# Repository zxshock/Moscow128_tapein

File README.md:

# Moscow128_tapein
4069 / 561LN2 based tape-in circuit for Moscow 128 boards to replace/substitute the convoluted original circuit.  
Note: This is intended for the 1989/replica boards not modernized variants. About the size of a DIP-20 socket.  

Measurements unchecked as of now.  
Preview has GND/VCC swapped - fixed in .brd

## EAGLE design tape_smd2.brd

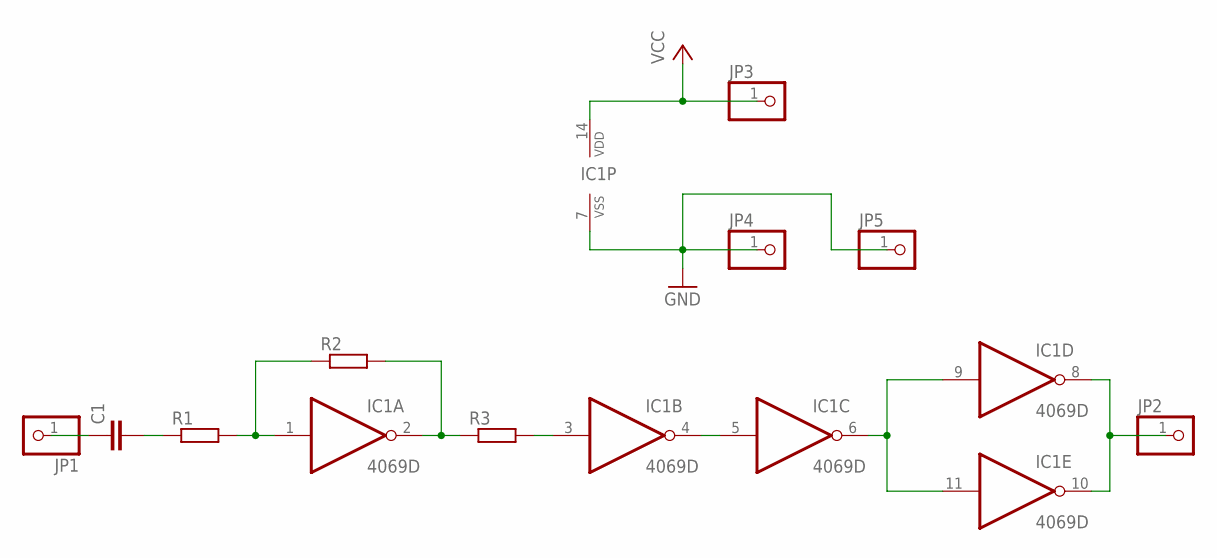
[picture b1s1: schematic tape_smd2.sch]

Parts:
C1: C-EUC0805; C0805
IC1: 4069D; SO14
JP1, JP2, JP3, JP4, JP5: PINHD-1X1; 1X01
R1, R2, R3: R-EU_R0805; R0805

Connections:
GND: IC1.7 (VSS), JP4.1, JP5.1
unnamed: C1.1, JP1.1
unnamed: C1.2, R1.1
unnamed: IC1.1 (I), R1.2, R2.1
unnamed: IC1.2 (O), R2.2, R3.1
unnamed: IC1.3 (I), R3.2
unnamed: IC1.4 (O), IC1.5 (I)
unnamed: IC1.6 (O), IC1.9 (I), IC1.11 (I)
unnamed: IC1.8 (O), IC1.10 (O), JP2.1
VCC: IC1.14 (VDD), JP3.1

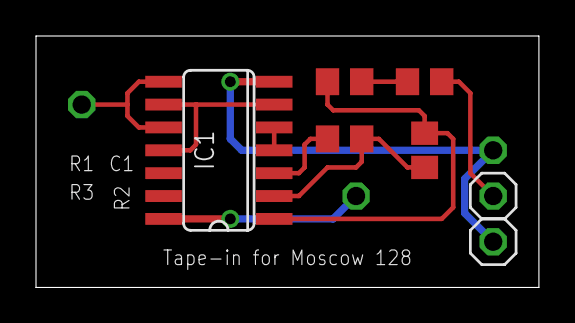
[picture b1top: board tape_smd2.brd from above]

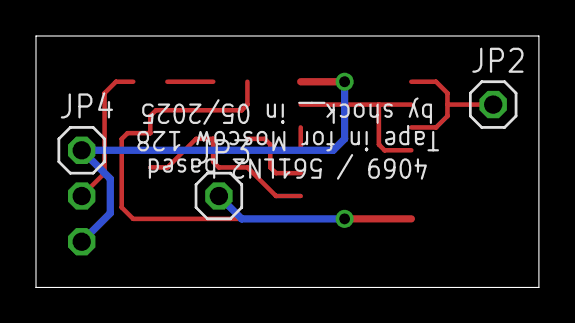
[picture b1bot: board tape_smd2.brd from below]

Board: 2 copper layers, 27.9 x 14.0 mm, 10 parts (3 on the bottom side), 10 nets.
